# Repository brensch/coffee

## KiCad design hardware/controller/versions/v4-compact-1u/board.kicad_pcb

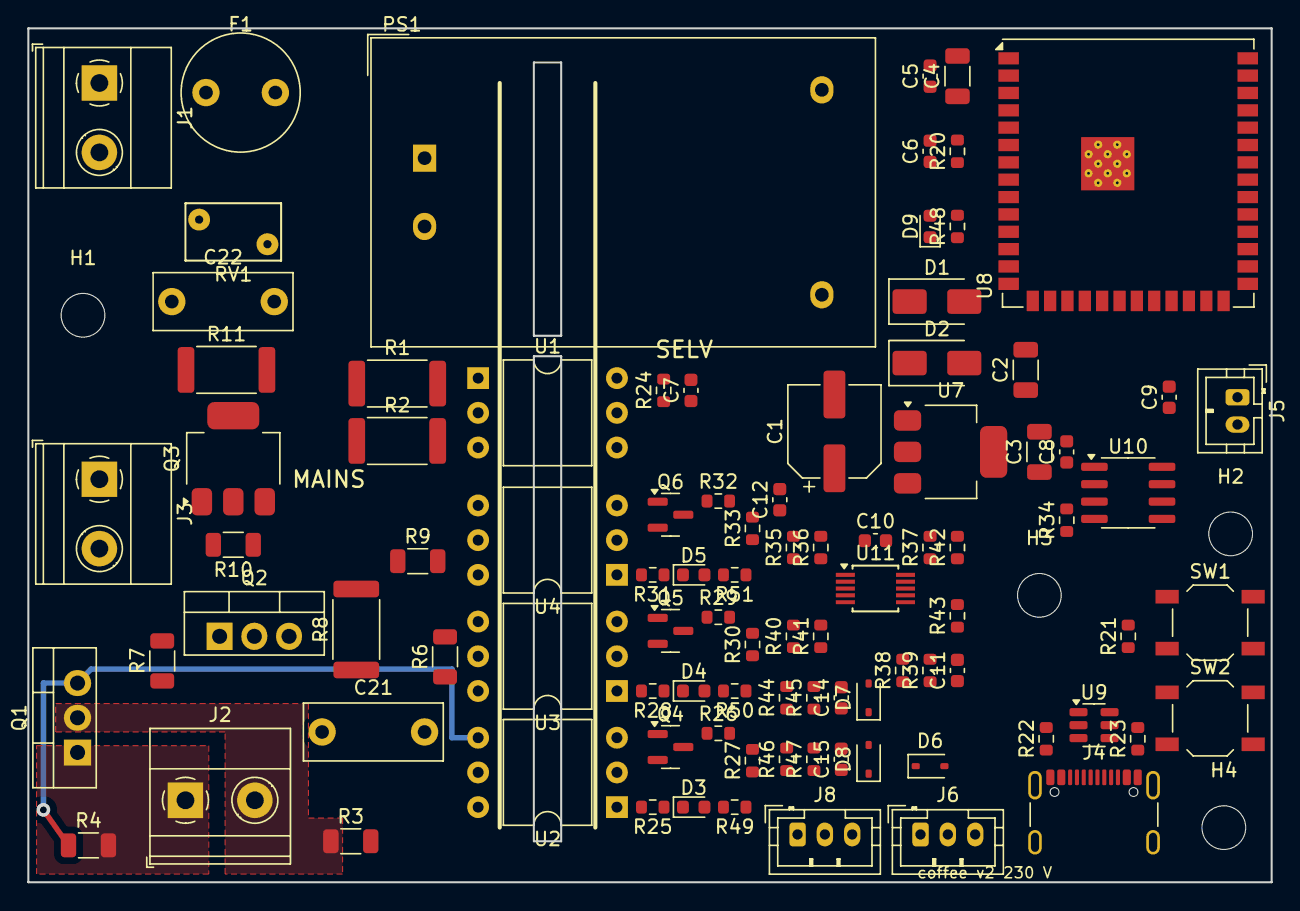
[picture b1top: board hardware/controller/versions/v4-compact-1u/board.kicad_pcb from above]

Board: 2 copper layers, 91.0 x 62.5 mm, 98 parts (0 on the bottom side), 63 nets.

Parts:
C1: 100uF 16V; CP_Elec_6.3x7.7
C2, C4: 10uF; C_1206_3216Metric
C3: 22uF 6.3V; C_1206_3216Metric
C5, C8, C10, C11, C12, C14, C15: 100nF; C_0603_1608Metric
C6: 1uF; C_0603_1608Metric
C7: 100pF; C_0603_1608Metric
C9: 10nF; C_0603_1608Metric
C21, C22: 10nF X2; C_Rect_L10.0mm_W4.0mm_P7.50mm_MKS4
D1, D2: SS14; D_SMA
D3: heater green; LED_0603_1608Metric
D4: pump green; LED_0603_1608Metric
D5: valve green; LED_0603_1608Metric
D6, D7, D8: PESD5V0S1BA; D_SOD-323
D9: status blue; LED_0603_1608Metric
F1: T500mA; Fuse_Littelfuse_372_D8.50mm
H1, H2, H3, H4: M3; MountingHole_3.2mm_M3
J1: Mains in; TerminalBlock_Phoenix_MKDS-1,5-2-5.08_1x02_P5.08mm_Horizont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
J2: Heater; TerminalBlock_Phoenix_MKDS-1,5-2-5.08_1x02_P5.08mm_Horizont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
J3: Pump / valve; TerminalBlock_Phoenix_MKDS-1,5-2-5.08_1x02_P5.08mm_Horizont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
J4: USB-C; USB_C_Receptacle_GCT_USB4105-xx-A_16P_TopMnt_Horizontal
J5: Thermocouple K; JST_PH_B2B-PH-K_1x02_P2.00mm_Vertical
J6: Pressure 0-1.6MPa; JST_PH_B3B-PH-K_1x03_P2.00mm_Vertical
J8: Switches; JST_PH_B3B-PH-K_1x03_P2.00mm_Vertical
PS1: HLK-PM05; Converter_ACDC_Hi-Link_HLK-PMxx
Q1: BTA16-600BW; TO-220-3_Vertical
Q2: BTA08-600CW; TO-220-3_Vertical
Q3: Z0109MN; SOT-223-3_TabPin2
Q4, Q5, Q6: AO3400A; SOT-23
R1, R2: 47k 1W; R_2512_6332Metric
R3, R6, R9: 360; R_1206_3216Metric
R4, R7, R10: 330; R_1206_3216Metric
R8, R11: 100 1W; R_2512_6332Metric
R20, R21, R34, R37, R44, R46: 10k; R_0603_1608Metric
R22, R23: 5.1k; R_0603_1608Metric
R24: 47k; R_0603_1608Metric
R25, R28, R31: 220; R_0603_1608Metric
R26, R29, R32: 100; R_0603_1608Metric
R27, R30, R33, R42, R43: 100k; R_0603_1608Metric
R35, R36: 4.7k; R_0603_1608Metric
R38, R40: 10k 0.1%; R_0603_1608Metric
R39, R41: 20k 0.1%; R_0603_1608Metric
R45, R47, R48, R49, R50, R51: 1k; R_0603_1608Metric
RV1: 10D561K; RV_Disc_D7mm_W4.2mm_P5mm
SW1: RESET; SW_SPST_TL3342
SW2: BOOT; SW_SPST_TL3342
U1: H11AA1; DIP-6_W10.16mm
U2, U3, U4: MOC3063; DIP-6_W10.16mm
U7: AMS1117-3.3; SOT-223-3_TabPin2
U8: ESP32-S3-WROOM-1U-N8; ESP32-S3-WROOM-1U
U9: USBLC6-2SC6; SOT-23-6
U10: MAX31855KASA+; SOIC-8_3.9x4.9mm_P1.27mm
U11: ADS1115IDGSR; MSOP-10_3x3mm_P0.5mm

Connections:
5V_PSU: D1.2, PS1.4
+3V3: C3.1, C4.1, C5.1, C8.1, C10.1, R20.1, R21.1, R24.1, R34.1, R35.1, R36.1, R37.1, R44.1, R46.1, U7.2, U8.2, U10.4, U11.8
+5V: C1.1, C2.1, D1.1, D2.1, J6.1, R25.1, R28.1, R31.1, R40.1, R49.1, R50.1, R51.1, U7.3
AC_L: F1.1, J1.1, Q2.2, Q3.2, R6.1, R8.1, R9.1, R11.1
AC_L_FUSED: F1.2, PS1.1, R1.1, RV1.1
AC_N: J1.2, PS1.2, R2.1, RV1.2
ADC_RDY: R37.2, U8.19, U11.2
AIN2_SPARE: R42.1, U11.6
AIN3_SPARE: R43.1, U11.7
CC1: J4.A5, R22.1
CC2: J4.B5, R23.1
EN: C6.1, R20.2, SW1.1, U8.3
GND: C1.2, C2.2, C3.2, C4.2, C5.2, C6.2, C7.2, C8.2, C10.2, C11.2, C12.2, C14.2, C15.2, D6.2, D7.2, D8.2, D9.1, J4.A1, J4.A12, J4.B1, J4.B12, J4.S1, J6.3, J8.3, PS1.3, Q4.2, Q5.2, Q6.2, R22.2, R23.2, R27.2, R30.2, R33.2, R39.2, R41.2, R42.2, R43.2, SW1.2, SW2.2, U1.4, U7.1, U8.1, U8.40, U8.41, U9.2, U10.1, U11.1, U11.3
HEATER_CMD: R26.1, U8.5
HEATER_DRV: D3.1, Q4.3, U2.2
HEATER_G: Q4.1, R26.2, R27.1
HEATER_GATE: Q1.3, R4.1, U2.4
HEATER_LED_A: D3.2, R49.2
HEATER_OPTO: R3.2, U2.6
HEATER_OPTO_A: R25.2, U2.1
HTR_A: J2.1, Q1.1, R4.2
HTR_B: J2.2, Q1.2, R3.1
IO0_BOOT: R21.2, SW2.1, U8.27
PUMP_CMD: R29.1, U8.6
PUMP_DRV: D4.1, Q5.3, U3.2
PUMP_G: Q5.1, R29.2, R30.1
PUMP_GATE: Q2.3, R7.1, U3.4
PUMP_L: C21.2, J3.2, Q2.1, R7.2
PUMP_LED_A: D4.2, R50.2
PUMP_OPTO: R6.2, U3.6
PUMP_OPTO_A: R28.2, U3.1
PUMP_SNUB: C21.1, R8.2
P_AIN0: C11.1, R38.2, R39.1, U11.4
P_SIG: D6.1, J6.2, R38.1
SCL: R36.2, U8.17, U11.10
SDA: R35.2, U8.12, U11.9
STATUS: R48.1, U8.31
STATUS_A: D9.2, R48.2
SW_BREW: D7.1, J8.1, R44.2, R45.1
SW_BREW_IN: C14.1, R45.2, U8.8
SW_STEAM: D8.1, J8.2, R46.2, R47.1
SW_STEAM_IN: C15.1, R47.2, U8.9
TC+: C9.1, J5.1, U10.3
TC-: C9.2, J5.2, U10.2
TC_CS: R34.2, U8.18, U10.6
TC_SCK: U8.20, U10.5
TC_SO: U8.21, U10.7
USB_D+: J4.A6, J4.B6, U8.14, U9.3, U9.4
USB_D-: J4.A7, J4.B7, U8.13, U9.1, U9.6
V5_AIN1: C12.1, R40.2, R41.1, U11.5
VALVE_CMD: R32.1, U8.7
VALVE_DRV: D5.1, Q6.3, U4.2
VALVE_G: Q6.1, R32.2, R33.1
VALVE_GATE: Q3.3, R10.1, U4.4
VALVE_L: C22.2, J3.1, Q3.1, R10.2
VALVE_LED_A: D5.2, R51.2
VALVE_OPTO: R9.2, U4.6
VALVE_OPTO_A: R31.2, U4.1
VALVE_SNUB: C22.1, R11.2
VBUS: D2.2, J4.A4, J4.A9, J4.B4, J4.B9, U9.5
ZC: C7.1, R24.2, U1.5, U8.4
ZC_A: R1.2, U1.1
ZC_B: R2.2, U1.2

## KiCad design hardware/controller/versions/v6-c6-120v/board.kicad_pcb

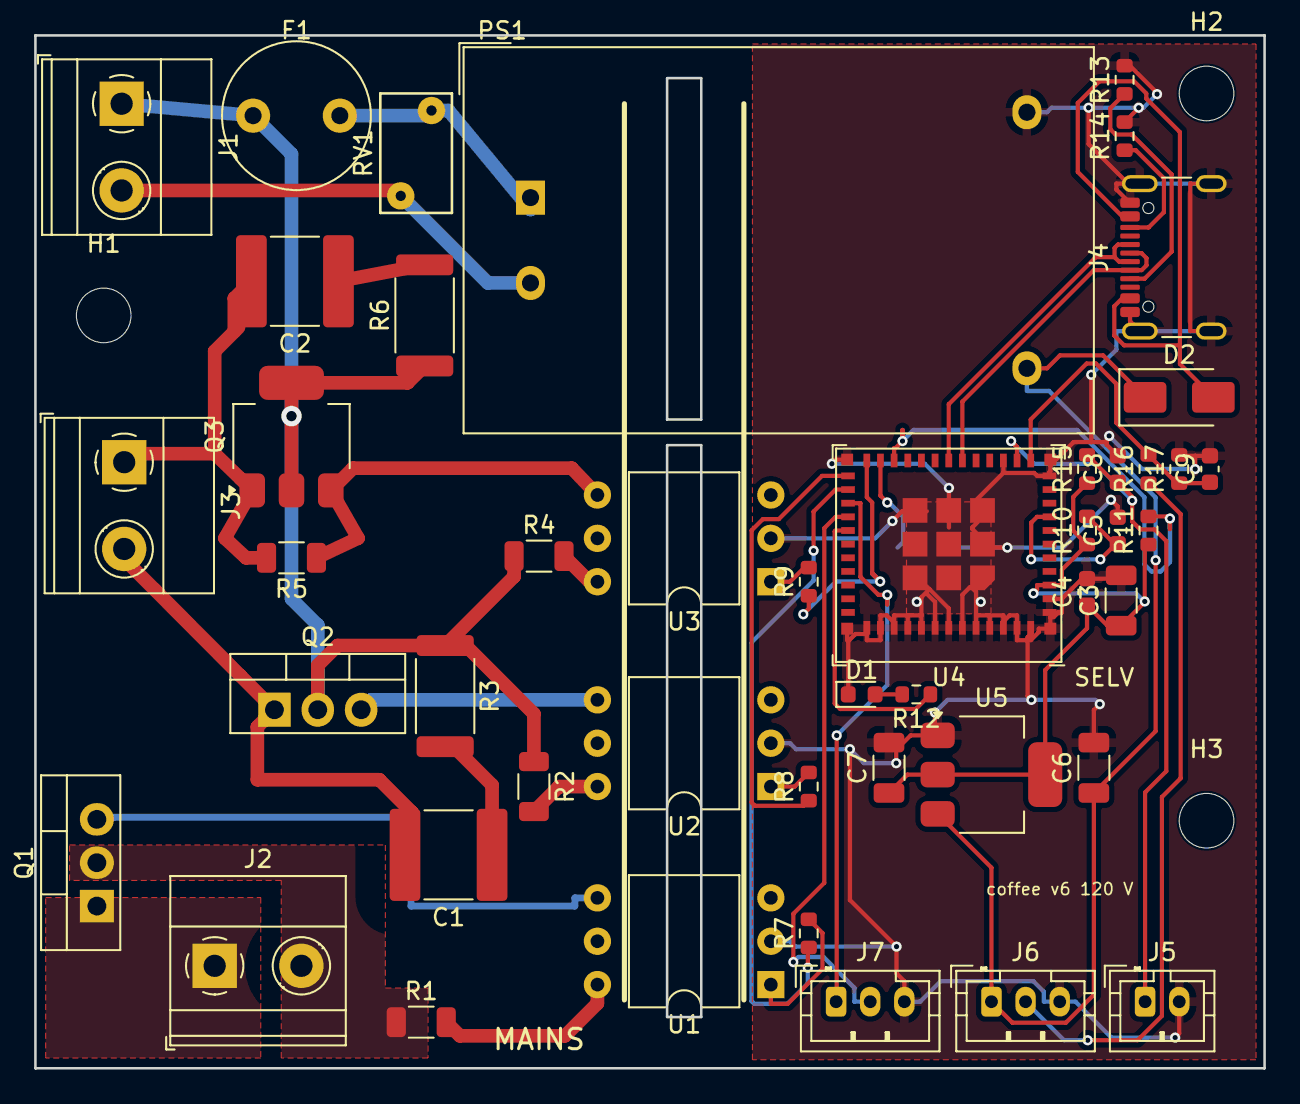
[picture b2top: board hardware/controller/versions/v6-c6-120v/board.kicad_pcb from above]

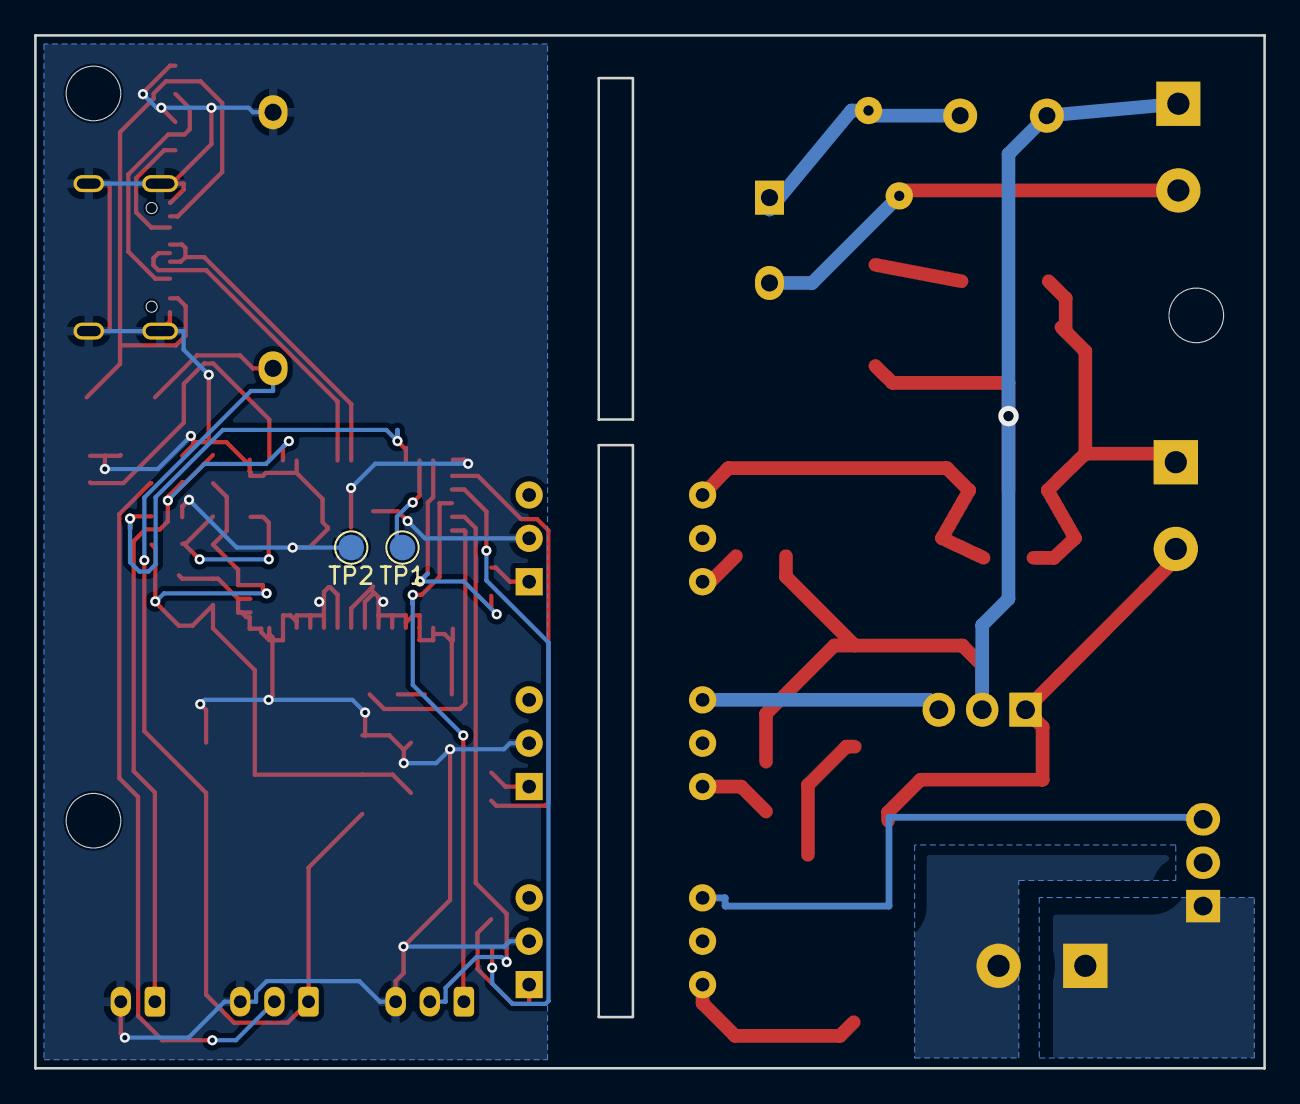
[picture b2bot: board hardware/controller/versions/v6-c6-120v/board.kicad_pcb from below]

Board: 2 copper layers, 72.0 x 60.5 mm, 51 parts (2 on the bottom side), 39 nets.

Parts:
C1, C2: 10nF X2; C_2220_5750Metric
C3: 10uF; C_1206_3216Metric
C4, C8, C9: 100nF; C_0603_1608Metric
C5: 1uF; C_0603_1608Metric
C6: 22uF 10V; C_1206_3216Metric
C7: 22uF 6.3V; C_1206_3216Metric
D1: green; LED_0603_1608Metric
D2: SS14; D_SMA
F1: T500mA; Fuse_Littelfuse_372_D8.50mm
H1, H2, H3: M3; MountingHole_3.2mm_M3
J1: Mains in; TerminalBlock_Phoenix_MKDS-1,5-2-5.08_1x02_P5.08mm_Horizont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
J2: Heater; TerminalBlock_Phoenix_MKDS-1,5-2-5.08_1x02_P5.08mm_Horizont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
J3: Valve / pump; TerminalBlock_Phoenix_MKDS-1,5-2-5.08_1x02_P5.08mm_Horizont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
J4: USB-C; USB_C_Receptacle_GCT_USB4105-xx-A_16P_TopMnt_Horizontal
J5: Thermistor; JST_PH_B2B-PH-K_1x02_P2.00mm_Vertical
J6: Pressure; JST_PH_B3B-PH-K_1x03_P2.00mm_Vertical
J7: Switches; JST_PH_B3B-PH-K_1x03_P2.00mm_Vertical
PS1: HLK-PM05; Converter_ACDC_Hi-Link_HLK-PMxx
Q1: BTA24-800BW; TO-220-3_Vertical
Q2: BTA08-800CW; TO-220-3_Vertical
Q3: Z0109NN; SOT-223-3_TabPin2
R1, R2, R4: 360; R_1206_3216Metric
R3, R6: 100 1W; R_2512_6332Metric
R5: 330; R_1206_3216Metric
R7, R8, R9: 150; R_0603_1608Metric
R10, R11: 10k; R_0603_1608Metric
R12: 1k; R_0603_1608Metric
R13, R14: 5.1k; R_0603_1608Metric
R15: 8.2k 0.1%; R_0603_1608Metric
R16: 10k 0.1%; R_0603_1608Metric
R17: 20k 0.1%; R_0603_1608Metric
RV1: 10D271K; RV_Disc_D7mm_W4.2mm_P5mm
TP1: BOOT; TestPoint_Pad_D1.5mm
TP2: GND; TestPoint_Pad_D1.5mm
U1, U2, U3: MOC3083; DIP-6_W10.16mm
U4: ESP32-C6-MINI-1U-H4; ESP32-C6-MINI-1U
U5: AMS1117-3.3; SOT-223-3_TabPin2

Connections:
+3V3: C3.1, C4.1, C7.1, R10.1, R11.1, R15.1, U4.3, U5.2
+5V: C6.1, D2.1, J6.1, PS1.4, U5.3
AC_L: F1.1, J1.1, Q2.2, Q3.2, R2.1, R3.1, R4.1, R6.1
AC_L_FUSED: F1.2, PS1.1, RV1.1
AC_N: J1.2, PS1.2, RV1.2
CC1: J4.A5, R13.1
CC2: J4.B5, R14.1
EN: C5.1, R10.2, U4.8
GND: C3.2, C4.2, C5.2, C6.2, C7.2, C8.2, C9.2, D1.1, J4.A1, J4.A12, J4.B1, J4.B12, J4.S1, J5.2, J6.3, J7.3, PS1.3, R13.2, R14.2, R17.2, TP2.1, U1.2, U2.2, U3.2, U4.1, U4.2, U4.11, U4.14, U4.36, U4.37, U4.38, U4.39, U4.40, U4.41, U4.42, U4.43, U4.44, U4.45, U4.46, U4.47, U4.48, U4.49, U4.50, U4.51, U4.52, U4.53, U5.1
HEATER_CMD: R7.1, U4.26
HEATER_GATE: Q1.3, U1.4
HEATER_OPTO: R1.2, U1.6
HEATER_OPTO_A: R7.2, U1.1
HTR_A: J2.1, Q1.1
HTR_B: J2.2, Q1.2, R1.1
IO8_STRAP: R11.2, U4.22
IO9_BOOT: TP1.1, U4.23
NTC: C8.1, J5.1, R15.2, U4.13
PUMP_CMD: R8.1, U4.25
PUMP_GATE: Q2.3, U2.4
PUMP_L: C1.2, J3.2, Q2.1
PUMP_OPTO: R2.2, U2.6
PUMP_OPTO_A: R8.2, U2.1
PUMP_SNUB: C1.1, R3.2
P_ADC: C9.1, R16.2, R17.1, U4.12
P_SIG: J6.2, R16.1
STATUS: R12.1, U4.29
STATUS_A: D1.2, R12.2
SW_BREW: J7.1, U4.27
SW_STEAM: J7.2, U4.28
USB_D+: J4.A6, J4.B6, U4.18
USB_D-: J4.A7, J4.B7, U4.17
VALVE_CMD: R9.1, U4.24
VALVE_GATE: Q3.3, R5.1, U3.4
VALVE_L: C2.2, J3.1, Q3.1, R5.2
VALVE_OPTO: R4.2, U3.6
VALVE_OPTO_A: R9.2, U3.1
VALVE_SNUB: C2.1, R6.2
VBUS: D2.2, J4.A4, J4.A9, J4.B4, J4.B9
